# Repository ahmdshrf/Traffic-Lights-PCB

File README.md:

# Traffic-Lights-PCB
- PCB Design for traffic Lights Control
- Used 4 IC 555 , 3 LEDs and Switch 
- Program used : EAGLE

## Schematic Desgin 

## Board Design

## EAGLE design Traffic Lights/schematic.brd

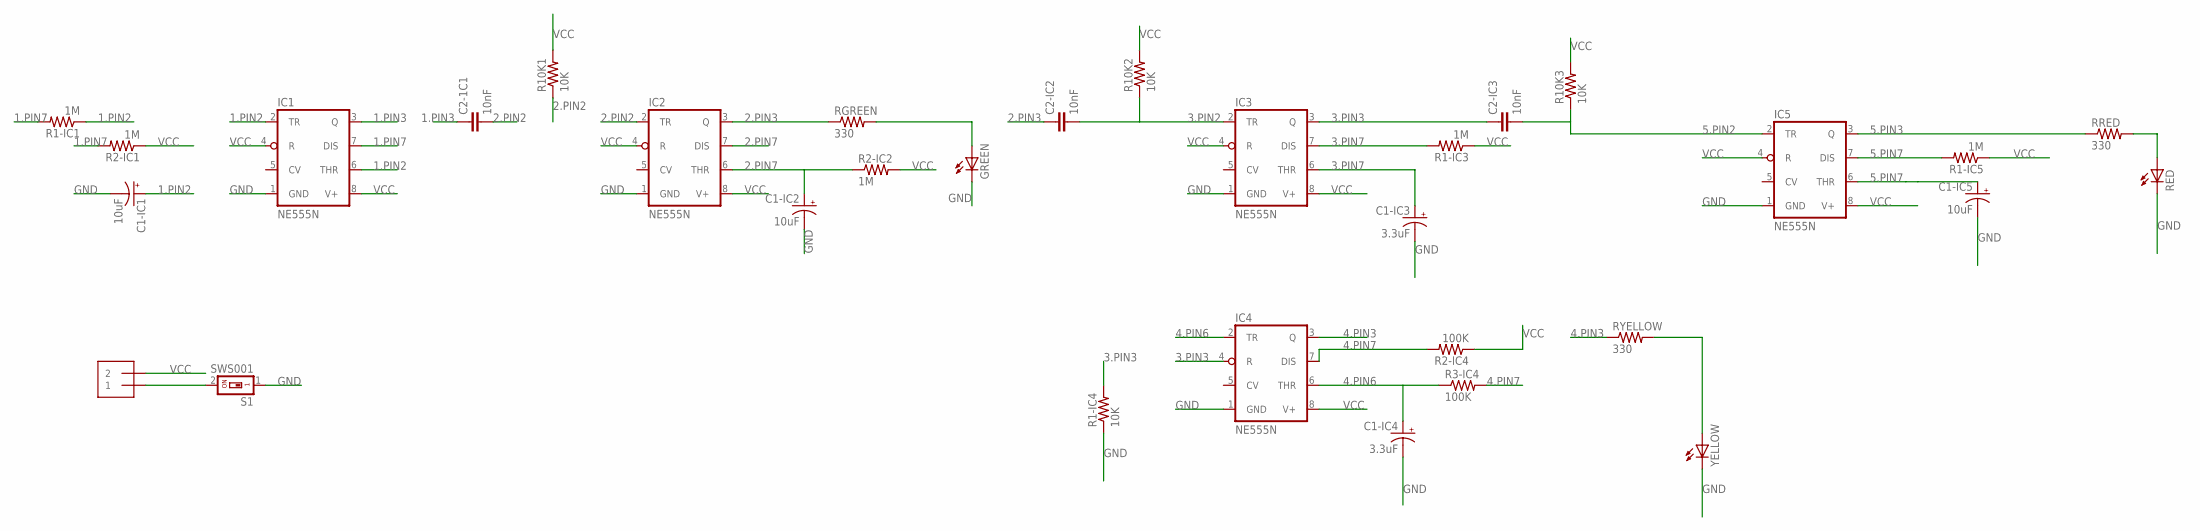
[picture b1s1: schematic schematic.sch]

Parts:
C1-IC1, C1-IC2, C1-IC5: 10uF; CPOL-RADIAL-2.5MM-6.5MM
C1-IC3, C1-IC4: 3.3uF; CPOL-RADIAL-2.5MM-6.5MM
C2-1C1, C2-IC2, C2-IC3: 10nF; 0603
GREEN: LED5MM
IC1, IC2, IC3, IC4, IC5: NE555N; DIL08-ROUND
J1: 1X2-3.5MM
R1-IC1, R1-IC3, R1-IC5, R2-IC1, R2-IC2: 1M; 0204/7
R1-IC4, R10K1, R10K2, R10K3: 10K; 0204/7
R2-IC4, R3-IC4: 100K; 0204/7
RED: LED5MM
RGREEN: 330; 0204/7
RRED: 330; 0204/7
RYELLOW: 330; 0204/7
S1: SWS001; SMS-001
YELLOW: LED5MM

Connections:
1.PIN2: C1-IC1.1 (+), IC1.2 (TR), IC1.6 (THR), R1-IC1.1
1.PIN3: C2-1C1.1, IC1.3 (Q)
1.PIN7: IC1.7 (DIS), R1-IC1.2, R2-IC1.2
2.PIN2: C2-1C1.2, IC2.2 (TR), R10K1.1
2.PIN3: C2-IC2.1, IC2.3 (Q), RGREEN.1
2.PIN7: C1-IC2.1 (+), IC2.6 (THR), IC2.7 (DIS), R2-IC2.1
3.PIN2: C2-IC2.2, IC3.2 (TR), R10K2.1
3.PIN3: C2-IC3.1, IC3.3 (Q), IC4.4 (R), R1-IC4.2
3.PIN7: C1-IC3.1 (+), IC3.6 (THR), IC3.7 (DIS), R1-IC3.2
4.PIN3: IC4.3 (Q), RYELLOW.1
4.PIN6: C1-IC4.1 (+), IC4.2 (TR), IC4.6 (THR), R3-IC4.1
4.PIN7: IC4.7 (DIS), R2-IC4.2, R3-IC4.2
5.PIN2: C2-IC3.2, IC5.2 (TR), R10K3.1
5.PIN3: IC5.3 (Q), RRED.1
5.PIN7: C1-IC5.1 (+), IC5.6 (THR), IC5.7 (DIS), R1-IC5.2
GND: C1-IC1.2 (-), C1-IC2.2 (-), C1-IC3.2 (-), C1-IC4.2 (-), C1-IC5.2 (-), GREEN.K (C), IC1.1 (GND), IC2.1 (GND), IC3.1 (GND), IC4.1 (GND), IC5.1 (GND), R1-IC4.1, RED.K (C), S1.1, YELLOW.K (C)
GNDBAT: J1.1, S1.2
GREEN: GREEN.A, RGREEN.2
RED: RED.A, RRED.2
VCC: IC1.4 (R), IC1.8 (V+), IC2.4 (R), IC2.8 (V+), IC3.4 (R), IC3.8 (V+), IC4.8 (V+), IC5.4 (R), IC5.8 (V+), J1.2, R1-IC3.1, R1-IC5.1, R2-IC1.1, R2-IC2.2, R2-IC4.1, R10K1.2, R10K2.2, R10K3.2
YELLOW: RYELLOW.2, YELLOW.A

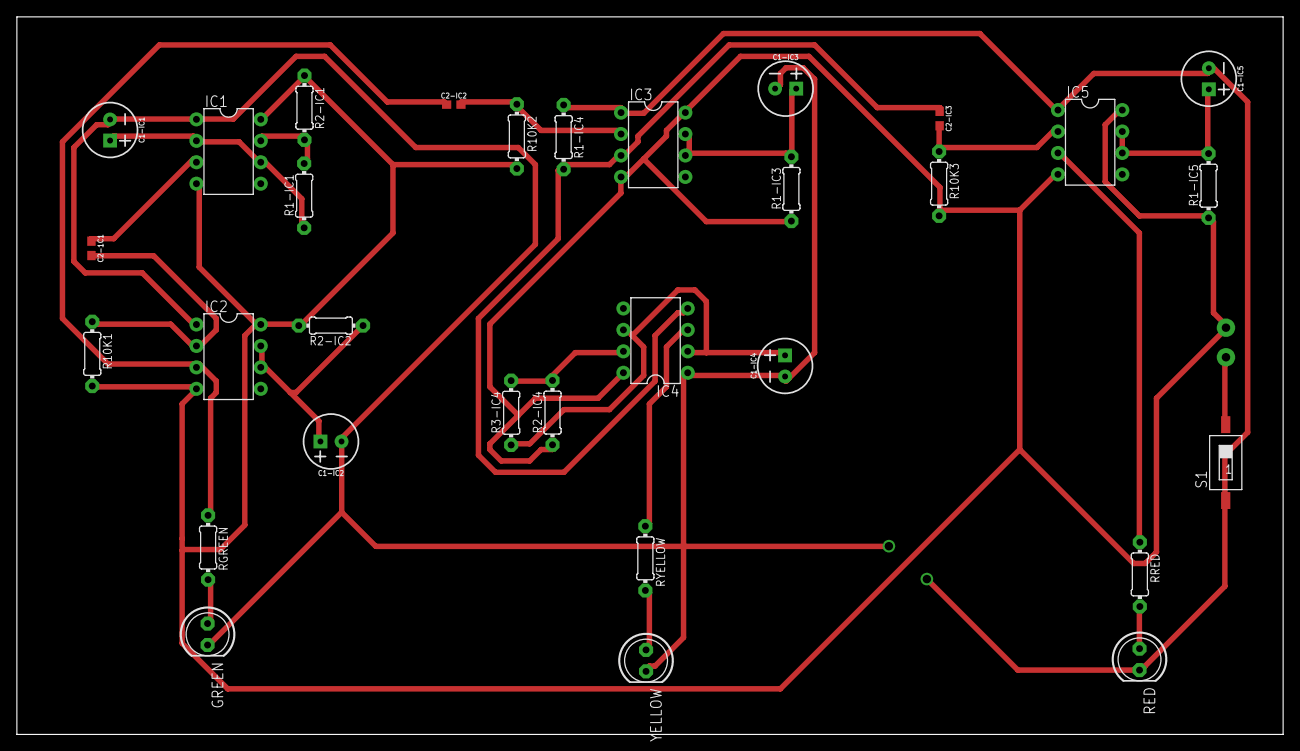
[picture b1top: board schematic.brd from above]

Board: 2 copper layers, 150.0 x 85.0 mm, 32 parts (1 on the bottom side), 21 nets.

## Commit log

2022-01-24 Adding Schematic and Board Design
2022-01-24 Add Description , Schematic and Board Captions

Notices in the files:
parts and their libraries:
SparkFun-Capacitors: Licensing: Creative Commons ShareAlike 4.0 International - https://creativecommons.org/licenses/by-sa/4.0
